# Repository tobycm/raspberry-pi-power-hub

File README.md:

# RP2040 + CYPD3177 Power Hub

one port (usb c) to rule them all!!! this board is designed to take a single USB-C input and negociate for your power needs. it can output 5v, 9v, 12v, or 20v at up to 3A. the usb c port is also connected to a RP2040 if you want more processing with the CYPD3177 through HPI.

## 3D render

## BOM

| Part Name | Quantity | Link |
| :--- | :---: | :--- |
| PCB | 1 | [JLCPCB](https://jlcpcb.com) |
| Stencil | 1 | [JLCPCB](https://jlcpcb.com) |
| RP2040 | 1 | [C2040](https://lcsc.com/product-detail/C2040.html) |
| CYPD3177-24LQ | 1 | [C5904158](https://lcsc.com/product-detail/C5904158.html) |
| W25Q32JVSS | 1 | [C82344](https://lcsc.com/product-detail/C82344.html) |
| GT-USB-7010AN | 1 | [C963370](https://lcsc.com/product-detail/C963370.html) |
| ABM8-272-T3\_C20625731 | 1 | [C20625731](https://lcsc.com/product-detail/C20625731.html) |
| TS24CA | 3 | [C393942](https://lcsc.com/product-detail/C393942.html) |
| AP63203WU-7 | 1 | [C780769](https://lcsc.com/product-detail/C780769.html) |
| Zener Diode | 2 | [C82088](https://lcsc.com/product-detail/C82088.html) |
| NPN | 1 | [C5338312](https://lcsc.com/product-detail/C5338312.html) |
| AOD409-HXY | 2 | [C6285771](https://lcsc.com/product-detail/C6285771.html) |
| Green Led | 2 | [C7496818](https://lcsc.com/product-detail/C7496818.html) |
| Amber Led | 2 | [C165983](https://lcsc.com/product-detail/C165983.html) |
| Red Led | 3 | [C965799](https://lcsc.com/product-detail/C965799.html) |
| 18pF | 2 | [C106202](https://lcsc.com/product-detail/C106202.html) |
| 100nF | 12 | [C60474](https://lcsc.com/product-detail/C60474.html) |
| 10uF | 3 | [C2762594](https://lcsc.com/product-detail/C2762594.html) |
| 1uF | 6 | [C1592](https://lcsc.com/product-detail/C1592.html) |
| 4.7uF | 1 | [C51205](https://lcsc.com/product-detail/C51205.html) |
| 4.7uH | 1 | [C41413058](https://lcsc.com/product-detail/C41413058.html) |
| 470ohm | 7 | [C25117](https://lcsc.com/product-detail/C25117.html) |
| 49.9kohm | 1 | [C25897](https://lcsc.com/product-detail/C25897.html) |
| 4.7kohm | 1 | [C25900](https://lcsc.com/product-detail/C25900.html) |
| 5.1kohm | 1 | [C25905](https://lcsc.com/product-detail/C25905.html) |
| 10kohm | 1 | [C60490](https://lcsc.com/product-detail/C60490.html) |
| 1kohm | 5 | [C106235](https://lcsc.com/product-detail/C106235.html) |
| 27ohm | 2 | [C138021](https://lcsc.com/product-detail/C138021.html) |
| Pin Headers | 1 | [C7501275](https://lcsc.com/product-detail/C7501275.html) |
| | |
| Total cost | 74.24 USD LCSC + 13.98 USD JLCPCB = 88.22 USD | |
| Soldering paste (cheaper than PCBA) | 1 | https://amazon.ca/dp/B0BLSJQPR6 |
| Total cost with soldering paste | 88.22 USD + 19.59 CAD = 102.43 USD | |

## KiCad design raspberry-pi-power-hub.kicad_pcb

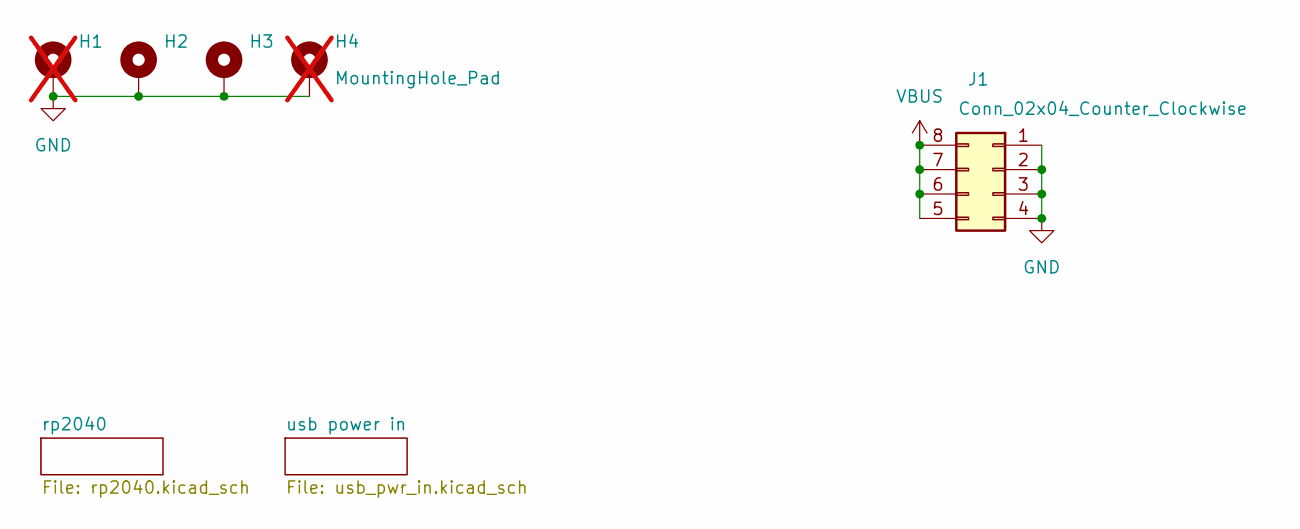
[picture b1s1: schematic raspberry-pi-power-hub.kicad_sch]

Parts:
H1, H4: MountingHole_Pad; MountingHole_2.2mm_M2_Pad; not fitted
H2, H3: MountingHole_Pad; MountingHole_2.2mm_M2_Pad
J1: Conn_02x04_Counter_Clockwise; PinHeader_2x04_P2.54mm_Vertical

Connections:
GND: H1.1, H2.1, H3.1, H4.1, J1.1, J1.2, J1.3, J1.4; also elsewhere on the board
VBUS: J1.5, J1.6, J1.7, J1.8; also elsewhere on the board

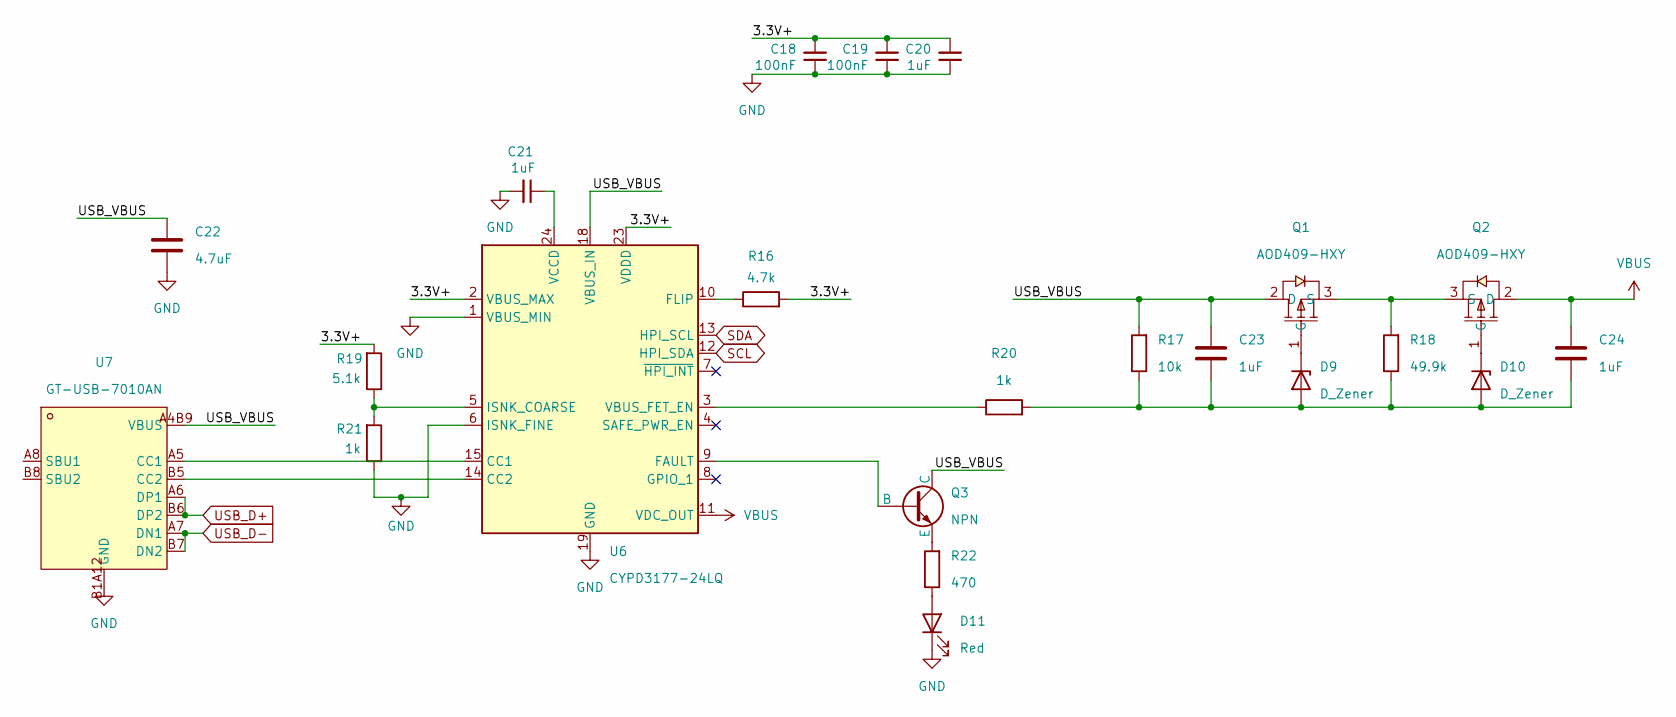
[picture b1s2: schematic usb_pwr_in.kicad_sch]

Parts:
C18, C19: 100nF; C_0402_1005Metric
C20, C21, C23, C24: 1uF; C_0603_1608Metric
C22: 4.7uF; C_1206_3216Metric
D9, D10: D_Zener; D_SOD-123
D11: Red; LED_0603_1608Metric_Pad1.05x0.95mm_HandSolder
Q1, Q2: AOD409-HXY; TO-252-2_L6.6-W6.1-P4.57-LS9.9-TL-CW; LCSC Part C6285771
Q3: NPN; SOT-23
R16: 4.7k; R_0402_1005Metric_Pad0.72x0.64mm_HandSolder
R17: 10k; R_0402_1005Metric_Pad0.72x0.64mm_HandSolder
R18: 49.9k; R_0402_1005Metric_Pad0.72x0.64mm_HandSolder
R19: 5.1k; R_0402_1005Metric_Pad0.72x0.64mm_HandSolder
R20, R21: 1k; R_0402_1005Metric_Pad0.72x0.64mm_HandSolder
R22: 470; R_0402_1005Metric_Pad0.72x0.64mm_HandSolder
U6: CYPD3177-24LQ; QFN-24-1EP_4x4mm_P0.5mm_EP2.75x2.75mm
U7: GT-USB-7010AN; USB-SMD_GT-USB-7010AN; LCSC Part C963370

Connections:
/usb power in/3.3V+: C18.2, C19.2, C20.2, R16.2, R19.2, U6.2 (VBUS_MAX), U6.23 (VDDD)
/usb power in/USB_VBUS: C22.1, C23.1, Q1.2 (D), Q3.1 (C), R17.2, U6.18 (VBUS_IN), U7.A4B9 (VBUS), U7.B4A9 (VBUS)
GND: C18.1, C19.1, C20.1, C21.2, C22.2, D11.1 (K), R21.1, U6.1 (VBUS_MIN), U6.6 (ISNK_FINE), U6.19 (GND), U6.22 (GND), U6.25 (GND), U7.13 (GND), U7.14 (GND), U7.15 (GND), U7.16 (GND), U7.A1B12 (GND), U7.B1A12 (GND); also elsewhere on the board
unnamed: D9.1 (K), Q1.1 (G)
unnamed: C23.2, C24.2, D9.2 (A), D10.2 (A), R17.1, R18.1, R20.2
unnamed: D10.1 (K), Q2.1 (G)
unnamed: D11.2 (A), R22.1
unnamed: Q1.3 (S), Q2.3 (S), R18.2
unnamed: Q3.2 (B), U6.9 (FAULT)
unnamed: Q3.3 (E), R22.2
unnamed: U6.15 (CC1), U7.A5 (CC1)
unnamed: U6.14 (CC2), U7.B5 (CC2)
unnamed: R16.1, U6.10 (FLIP)
unnamed: R19.1, R21.2, U6.5 (ISNK_COARSE)
unnamed: R20.1, U6.3 (VBUS_FET_EN)
unnamed: C21.1, U6.24 (VCCD)
SCL: U6.12 (HPI_SDA); also elsewhere on the board
SDA: U6.13 (HPI_SCL); also elsewhere on the board
USB_D+: U7.A6 (DP1), U7.B6 (DP2); also elsewhere on the board
USB_D-: U7.A7 (DN1), U7.B7 (DN2); also elsewhere on the board
VBUS: C24.1, Q2.2 (D), U6.11 (VDC_OUT); also elsewhere on the board

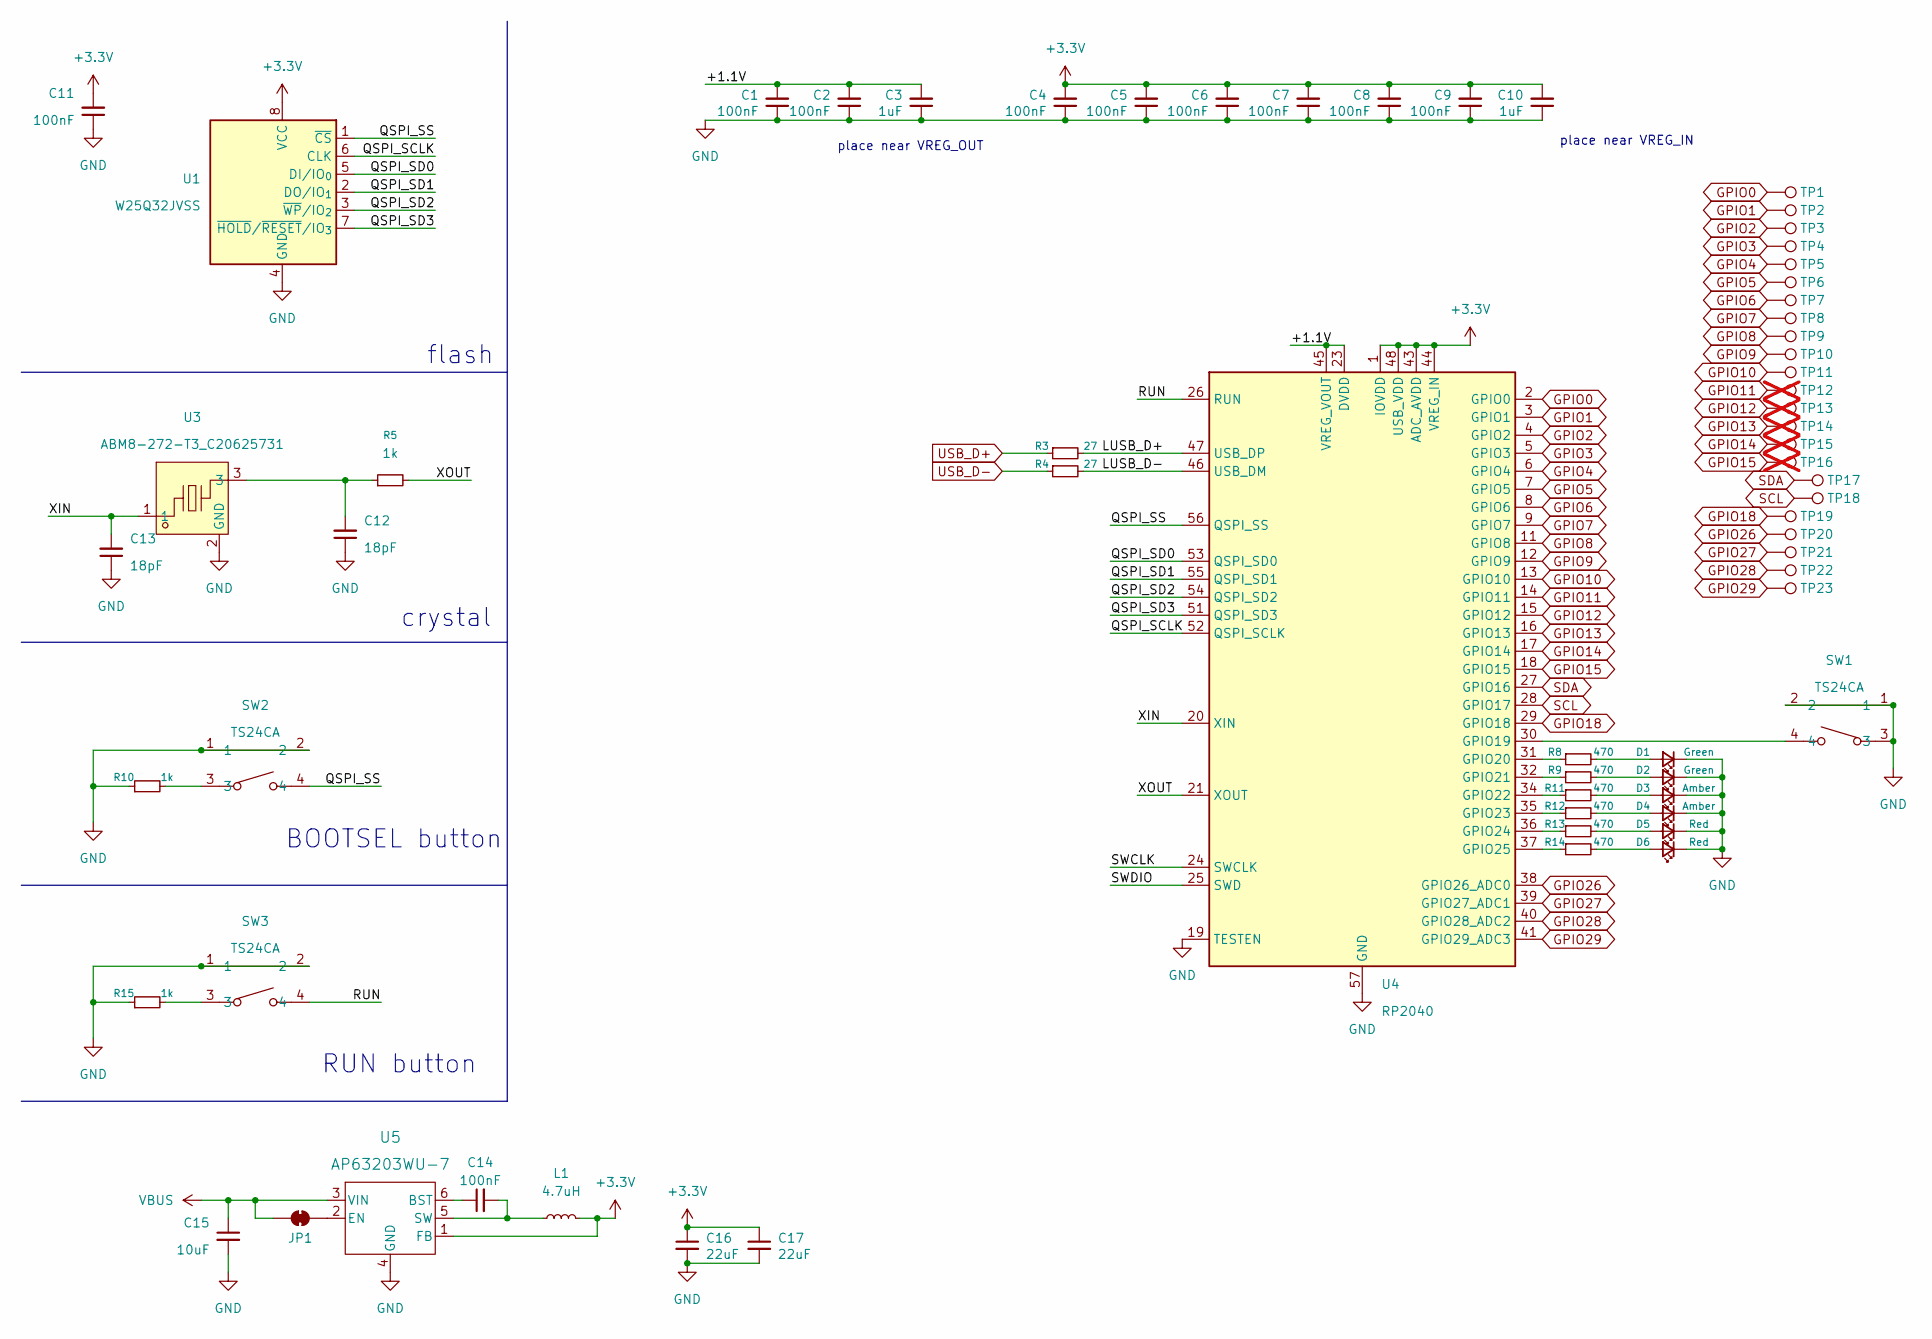
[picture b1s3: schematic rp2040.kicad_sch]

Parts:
C1, C2, C4, C5, C6, C7, C8, C9, C11, C14: 100nF; C_0402_1005Metric
C3, C10: 1uF; C_0603_1608Metric
C12, C13: 18pF; C_0402_1005Metric
C15: 10uF; C_0805_2012Metric
C16, C17: 22uF; C_0603_1608Metric
D1, D2: Green; LED_0603_1608Metric_Pad1.05x0.95mm_HandSolder
D3, D4: Amber; LED_0603_1608Metric_Pad1.05x0.95mm_HandSolder
D5, D6: Red; LED_0603_1608Metric_Pad1.05x0.95mm_HandSolder
JP1: SolderJumper_2_Bridged; SolderJumper-2_P1.3mm_Bridged_RoundedPad1.0x1.5mm
L1: 4.7uH; IND-SMD_L5.4-W5.2_CMLE051E
R3, R4: 27; R_0402_1005Metric_Pad0.72x0.64mm_HandSolder
R5, R10, R15: 1k; R_0402_1005Metric_Pad0.72x0.64mm_HandSolder
R8, R9, R11, R12, R13, R14: 470; R_0402_1005Metric_Pad0.72x0.64mm_HandSolder
SW1, SW2, SW3: TS24CA; SW-SMD_TS24CA; LCSC Part C393942
TP1, TP2, TP3, TP4, TP5, TP6, TP7, TP8, TP9, TP10, TP11, TP17, TP18, TP19, TP20, TP21, TP22, TP23: TestPoint; TestPoint_Pad_D1.5mm
TP12, TP13, TP14, TP15, TP16: TestPoint; TestPoint_Pad_D1.5mm; not fitted
U1: W25Q32JVSS; SOIC-8_5.3x5.3mm_P1.27mm
U3: ABM8-272-T3_C20625731; CRYSTAL-SMD_4P-L3.2-W2.5-BL; LCSC Part C20625731
U4: RP2040; QFN-56-1EP_7x7mm_P0.4mm_EP3.2x3.2mm
U5: AP63203WU-7; AP63203WU-7_DIO

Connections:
+3.3V: C4.2, C5.2, C6.2, C7.2, C8.2, C9.2, C10.2, C11.2, C16.1, C17.1, L1.2, U1.8 (VCC), U4.1 (IOVDD), U4.10 (IOVDD), U4.22 (IOVDD), U4.33 (IOVDD), U4.42 (IOVDD), U4.43 (ADC_AVDD), U4.44 (VREG_IN), U4.48 (USB_VDD), U4.49 (IOVDD), U5.1 (FB)
/rp2040/+1.1V: C1.2, C2.2, C3.2, U4.23 (DVDD), U4.45 (VREG_VOUT), U4.50 (DVDD)
/rp2040/LUSB_D+: R3.2, U4.47 (USB_DP)
/rp2040/LUSB_D-: R4.2, U4.46 (USB_DM)
/rp2040/QSPI_SCLK: U1.6 (CLK), U4.52 (QSPI_SCLK)
/rp2040/QSPI_SD0: U1.5 (DI/IO_{0}), U4.53 (QSPI_SD0)
/rp2040/QSPI_SD1: U1.2 (DO/IO_{1}), U4.55 (QSPI_SD1)
/rp2040/QSPI_SD2: U1.3 (~WP/IO_{2}), U4.54 (QSPI_SD2)
/rp2040/QSPI_SD3: U1.7 (~HOLD/~RESET/IO_{3}), U4.51 (QSPI_SD3)
/rp2040/QSPI_SS: SW2.4, U1.1 (~CS), U4.56 (QSPI_SS)
/rp2040/RUN: SW3.4, U4.26 (RUN)
/rp2040/SWCLK: U4.24 (SWCLK)
/rp2040/SWDIO: U4.25 (SWD)
/rp2040/XIN: C13.2, U3.1, U4.20 (XIN)
/rp2040/XOUT: R5.2, U4.21 (XOUT)
GND: C1.1, C2.1, C3.1, C4.1, C5.1, C6.1, C7.1, C8.1, C9.1, C10.1, C11.1, C12.1, C13.1, C15.2, C16.2, C17.2, D1.1 (K), D2.1 (K), D3.1 (K), D4.1 (K), D5.1 (K), D6.1 (K), R10.1, R15.1, SW1.1, SW1.2, SW1.3, SW2.1, SW2.2, SW3.1, SW3.2, U1.4 (GND), U3.2 (GND), U3.4 (GND), U4.19 (TESTEN), U4.57 (GND), U5.4 (GND); also elsewhere on the board
GPIO0: TP1.1, U4.2 (GPIO0)
GPIO1: TP2.1, U4.3 (GPIO1)
GPIO2: TP3.1, U4.4 (GPIO2)
GPIO3: TP4.1, U4.5 (GPIO3)
GPIO4: TP5.1, U4.6 (GPIO4)
GPIO5: TP6.1, U4.7 (GPIO5)
GPIO6: TP7.1, U4.8 (GPIO6)
GPIO7: TP8.1, U4.9 (GPIO7)
GPIO8: TP9.1, U4.11 (GPIO8)
GPIO9: TP10.1, U4.12 (GPIO9)
GPIO10: TP11.1, U4.13 (GPIO10)
GPIO11: TP12.1, U4.14 (GPIO11)
GPIO12: TP13.1, U4.15 (GPIO12)
GPIO13: TP14.1, U4.16 (GPIO13)
GPIO14: TP15.1, U4.17 (GPIO14)
GPIO15: TP16.1, U4.18 (GPIO15)
GPIO18: TP19.1, U4.29 (GPIO18)
GPIO26: TP20.1, U4.38 (GPIO26_ADC0)
GPIO27: TP21.1, U4.39 (GPIO27_ADC1)
GPIO28: TP22.1, U4.40 (GPIO28_ADC2)
GPIO29: TP23.1, U4.41 (GPIO29_ADC3)
unnamed: C12.2, R5.1, U3.3
unnamed: D1.2 (A), R8.2
unnamed: D2.2 (A), R9.2
unnamed: D3.2 (A), R11.2
unnamed: D4.2 (A), R12.2
unnamed: D5.2 (A), R13.2
unnamed: D6.2 (A), R14.2
unnamed: JP1.2 (B), U5.2 (EN)
unnamed: R10.2, SW2.3
unnamed: R15.2, SW3.3
unnamed: SW1.4, U4.30 (GPIO19)
unnamed: R8.1, U4.31 (GPIO20)
unnamed: R9.1, U4.32 (GPIO21)
unnamed: R11.1, U4.34 (GPIO22)
unnamed: R12.1, U4.35 (GPIO23)
unnamed: R13.1, U4.36 (GPIO24)
unnamed: R14.1, U4.37 (GPIO25)
unnamed: C14.1, U5.6 (BST)
unnamed: C14.2, L1.1, U5.5 (SW)
SCL: TP18.1, U4.28 (GPIO17); also elsewhere on the board
SDA: TP17.1, U4.27 (GPIO16); also elsewhere on the board
USB_D+: R3.1; also elsewhere on the board
USB_D-: R4.1; also elsewhere on the board
VBUS: C15.1, JP1.1 (A), U5.3 (VIN); also elsewhere on the board

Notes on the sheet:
place near VREG_OUT
place near VREG_IN
RUN button
crystal
flash
BOOTSEL button

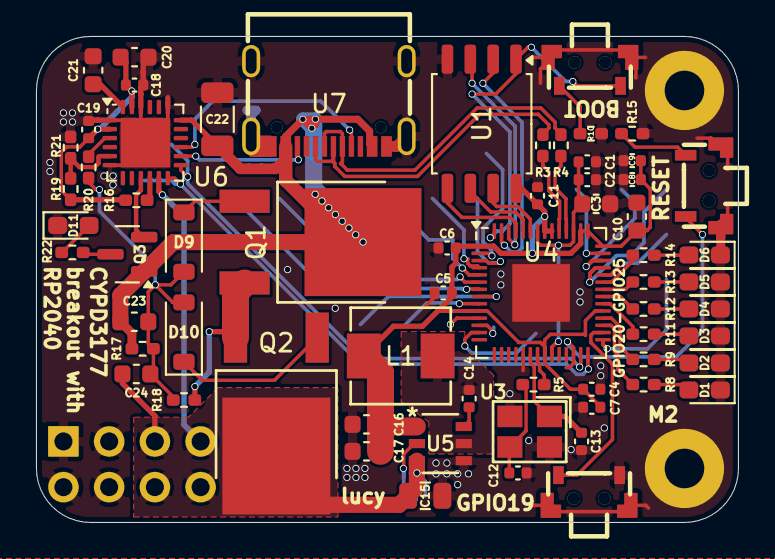
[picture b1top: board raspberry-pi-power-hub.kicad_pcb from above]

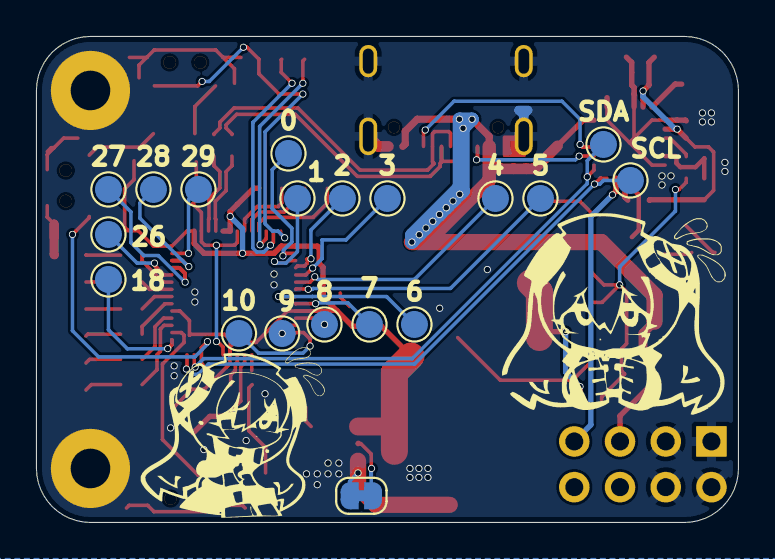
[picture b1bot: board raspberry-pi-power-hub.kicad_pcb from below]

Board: 2 copper layers, 39.0 x 27.0 mm, 86 parts (20 on the bottom side), 69 nets.

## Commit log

2025-06-25 getting started :fire:
2025-06-25 add metadata to journal
2025-06-26 rp2040!!
2025-06-27 small rp2040 changes and the cypd3177
2025-06-30 peak schematic
2025-07-21 finished pcb routing yay
2025-07-26 fixed via size woohoo!
2025-07-26 add bom
2025-07-26 add Readme
2025-07-26 schematic
2025-07-28 add total cost
2025-07-29 add stencil
2025-07-29 update bom with shipping and soldering paste
